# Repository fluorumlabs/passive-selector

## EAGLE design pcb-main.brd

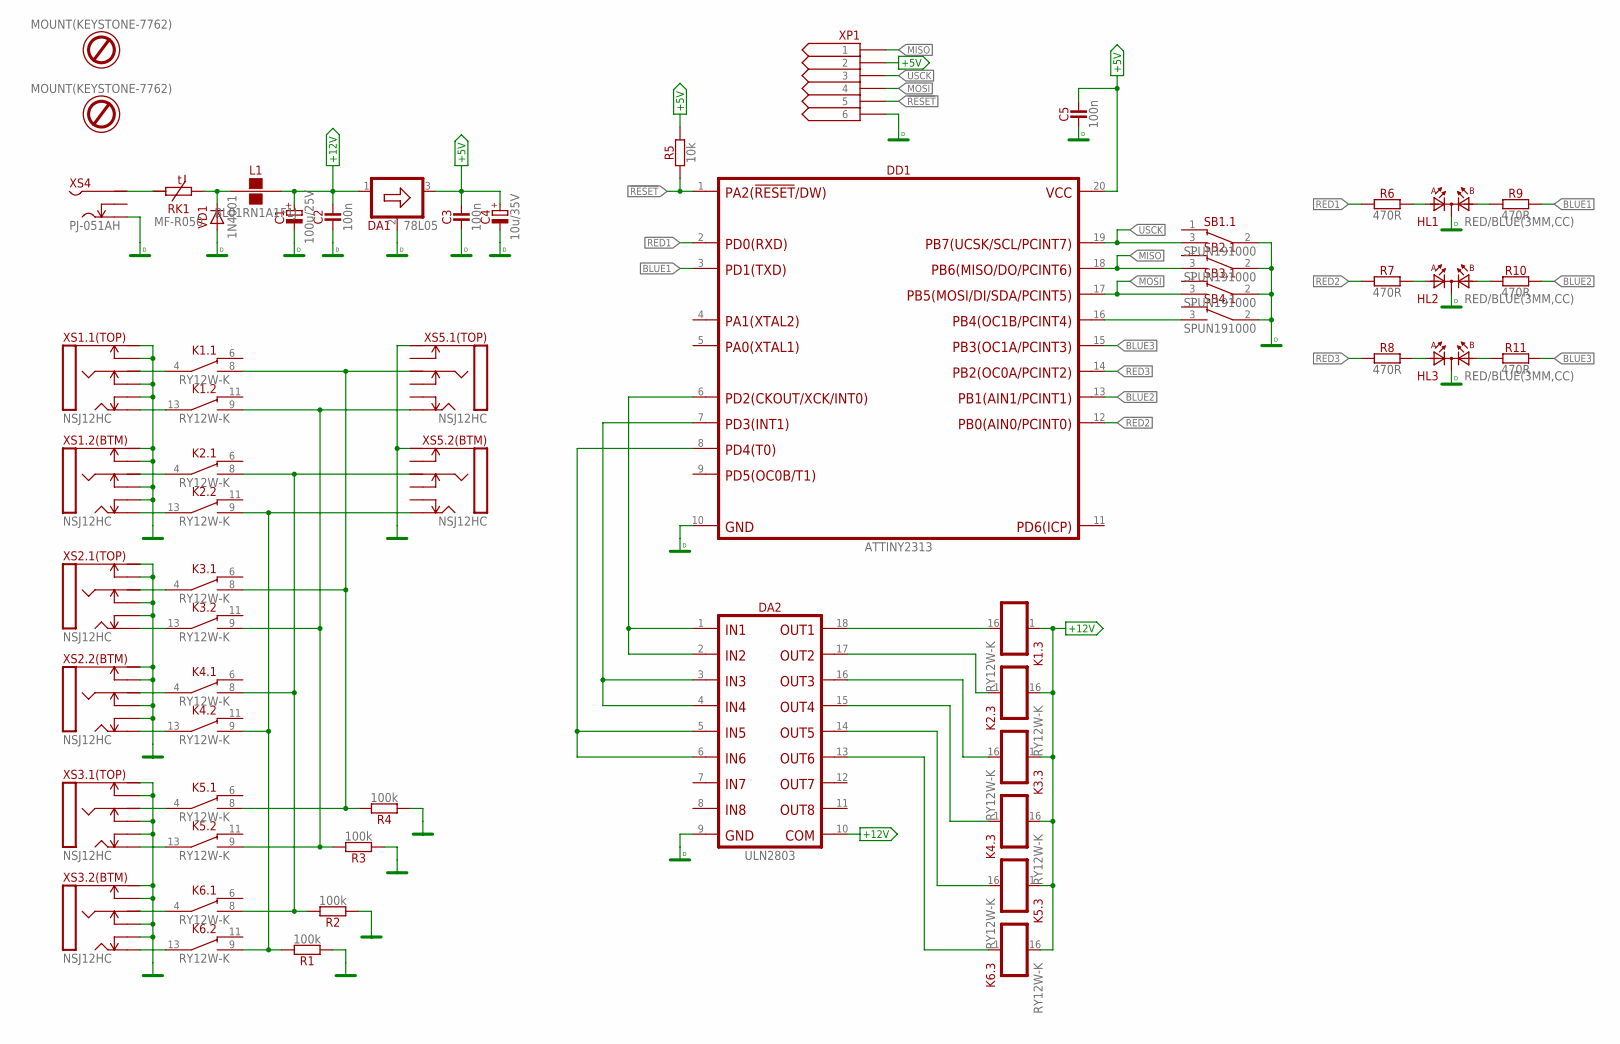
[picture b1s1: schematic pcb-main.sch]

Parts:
C1: 100u/25V; E2,5-7
C2, C3, C5: 100n; C050-024X044
C4: 10u/35V; E2-5
DA1: 78L05; TO92
DA2: ULN2803; DIP-18
DD1: ATTINY2313; DIP-20
HL1, HL2, HL3: RED/BLUE(3MM,CC); DUOLED3MM-H
K1, K2, K3, K4, K5, K6: RY12W-K; RY
L1: BL01RN1A1F1J; BL01RN1A
O1, O2: MOUNT(KEYSTONE-7762); KEYSTONE-7762
R1, R2, R3, R4: 100k; R-0207/10
R5: 10k; R-0207/10
R6, R7, R8, R9, R10, R11: 470R; R-0207/10
RK1: MF-R050; S05K40
SB1, SB2, SB3, SB4: SPUN191000; SPUN-DPDT
VD1: 1N4001; DO41-10
XP1: CONN-6-IDC-LITE; ML6-NO-SHROWD
XS1, XS2, XS3, XS5: NSJ12HC
XS4: PJ-051AH

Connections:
!RESET: DD1.1 (PA2(!RESET/DW)), R5.1, XP1.5
+5V: C3.2, C4.+, C5.2, DA1.3 (OUT), DD1.20 (VCC), R5.2, XP1.2
+12V: C1.+, C2.2, DA1.1 (IN), DA2.10, K1.1 (+), K2.16 (-), K3.1 (+), K4.16 (-), K5.1 (+), K6.16 (-), L1.2
BLUE1: DD1.3 (PD1(TXD)), R9.2
BLUE2: DD1.13 (PB1(AIN1/PCINT1)), R10.2
BLUE3: DD1.15 (PB3(OC1A/PCINT3)), R11.2
DGND: C1.-, C2.1, C3.1, C4.-, C5.1, DA1.2 (GND), DA2.9, DD1.10 (GND), HL1.K, HL2.K, HL3.K, SB1.2 (CM), SB2.2 (CM), SB3.2 (CM), SB4.2 (CM), VD1.A, XP1.6, XS4.3 (S)
GND: R1.1, R2.1, R3.1, R4.1, XS1.RNB (RN), XS1.RNT (RN), XS1.SB (S), XS1.SNB (SN), XS1.SNT (SN), XS1.ST (S), XS1.TNB (TN), XS1.TNT (TN), XS2.RNB (RN), XS2.RNT (RN), XS2.SB (S), XS2.SNB (SN), XS2.SNT (SN), XS2.ST (S), XS2.TNB (TN), XS2.TNT (TN), XS3.RNB (RN), XS3.RNT (RN), XS3.SB (S), XS3.SNB (SN), XS3.SNT (SN), XS3.ST (S), XS3.TNB (TN), XS3.TNT (TN), XS5.SB (S), XS5.ST (S)
MISO: DD1.18 (PB6(MISO/DO/PCINT6)), SB2.3 (NO), XP1.1
MOSI: DD1.17 (PB5(MOSI/DI/SDA/PCINT5)), SB3.3 (NO), XP1.4
unnamed: K1.13 (CM), XS1.TT (T)
unnamed: RK1.1 (A), XS4.1
unnamed: L1.1, RK1.2 (E), VD1.C
unnamed: K1.4 (CM), XS1.RT (R)
unnamed: K2.4 (CM), XS1.RB (R)
unnamed: K2.13 (CM), XS1.TB (T)
unnamed: K3.4 (CM), XS2.RT (R)
unnamed: K3.13 (CM), XS2.TT (T)
unnamed: K4.13 (CM), XS2.TB (T)
unnamed: K4.4 (CM), XS2.RB (R)
unnamed: K6.13 (CM), XS3.TB (T)
unnamed: K6.4 (CM), XS3.RB (R)
unnamed: K5.13 (CM), XS3.TT (T)
unnamed: K5.4 (CM), XS3.RT (R)
unnamed: K1.8 (NO), K3.8 (NO), K5.8 (NO), R4.2, XS5.RT (R)
unnamed: K2.9 (NO), K4.9 (NO), K6.9 (NO), R1.2, XS5.TB (T)
unnamed: K2.8 (NO), K4.8 (NO), K6.8 (NO), R2.2, XS5.RB (R)
unnamed: K1.9 (NO), K3.9 (NO), K5.9 (NO), R3.2, XS5.TT (T)
unnamed: DD1.16 (PB4(OC1B/PCINT4)), SB4.3 (NO)
unnamed: HL1.A1, R6.2
unnamed: HL2.A1, R7.2
unnamed: HL1.A2, R9.1
unnamed: HL2.A2, R10.1
unnamed: HL3.A1, R8.2
unnamed: HL3.A2, R11.1
unnamed: DA2.1, DA2.2, DD1.6 (PD2(CKOUT/XCK/INT0))
unnamed: DA2.3, DA2.4, DD1.7 (PD3(INT1))
unnamed: DA2.5, DA2.6, DD1.8 (PD4(T0))
unnamed: DA2.18, K1.16 (-)
unnamed: DA2.17, K2.1 (+)
unnamed: DA2.16, K3.16 (-)
unnamed: DA2.15, K4.1 (+)
unnamed: DA2.14, K5.16 (-)
unnamed: DA2.13, K6.1 (+)
RED1: DD1.2 (PD0(RXD)), R6.1
RED2: DD1.12 (PB0(AIN0/PCINT0)), R7.1
RED3: DD1.14 (PB2(OC0A/PCINT2)), R8.1
USCK: DD1.19 (PB7(UCSK/SCL/PCINT7)), SB1.3 (NO), XP1.3

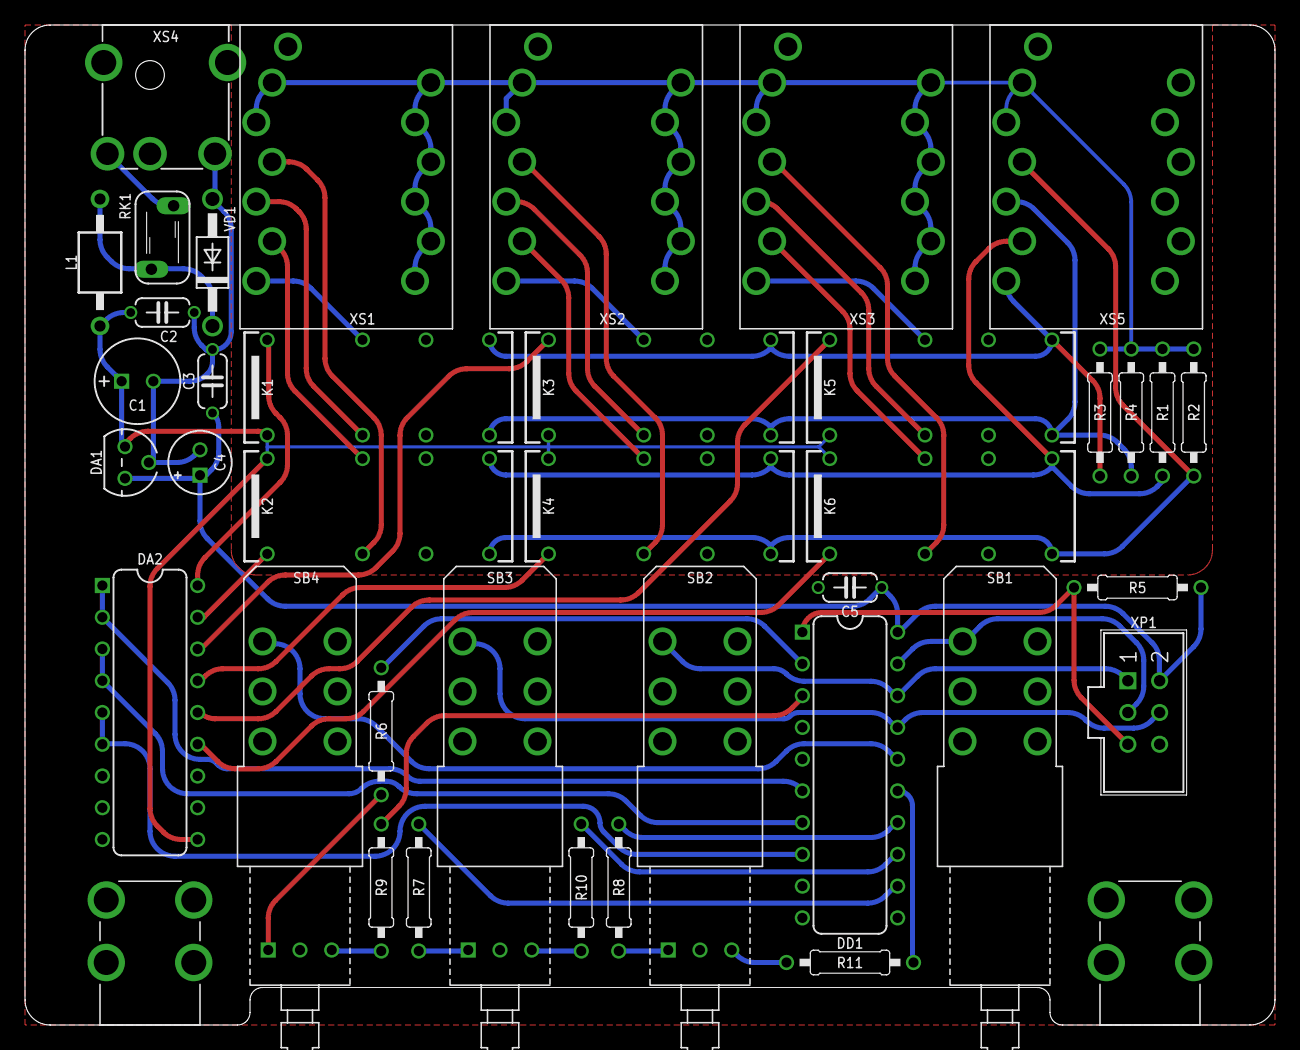
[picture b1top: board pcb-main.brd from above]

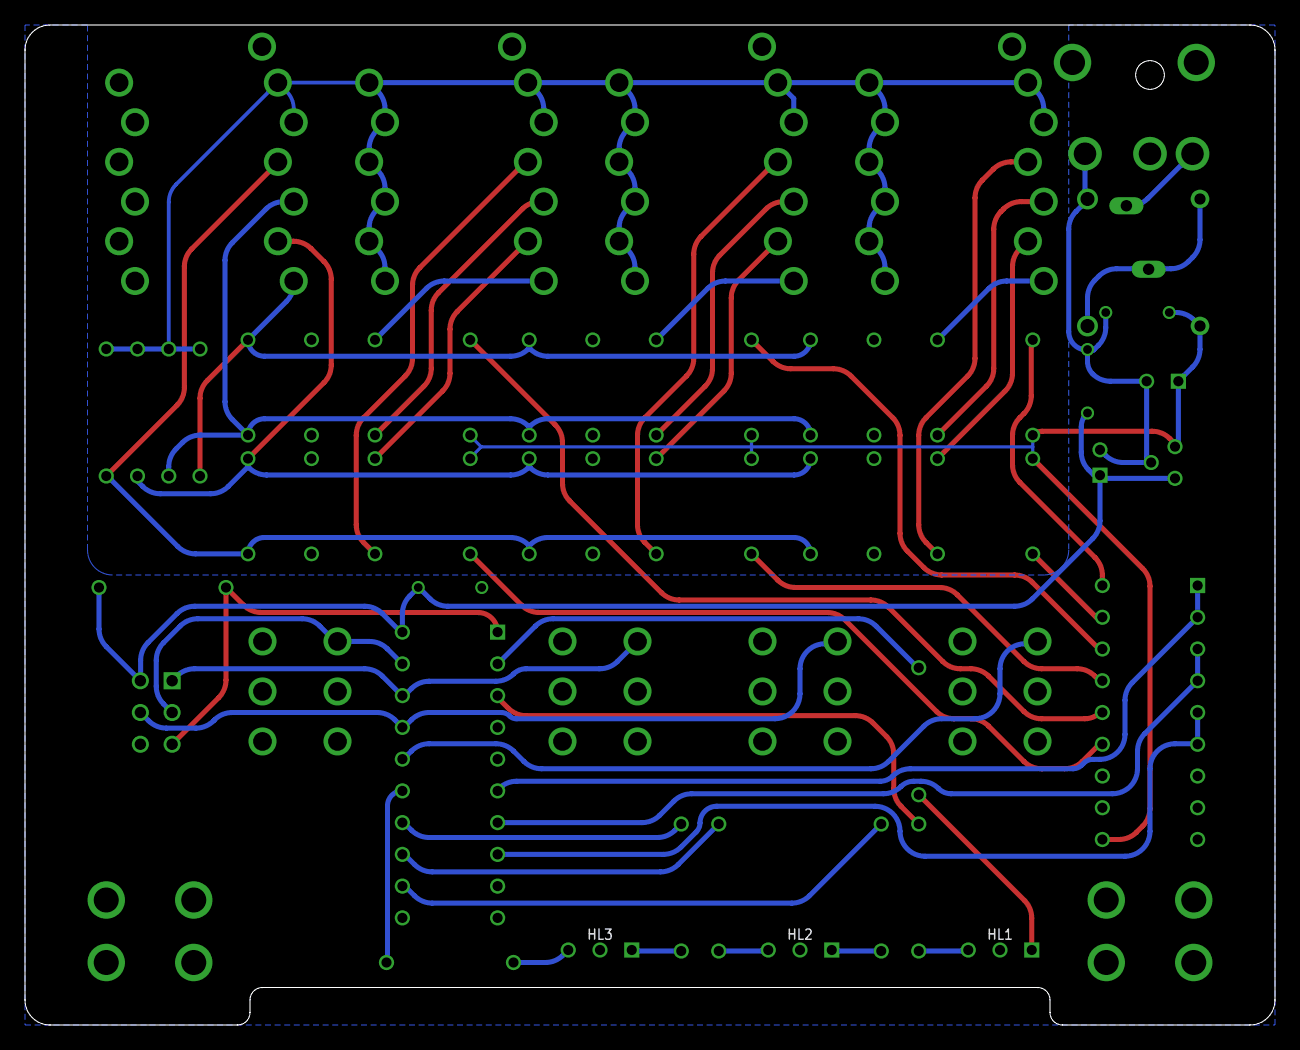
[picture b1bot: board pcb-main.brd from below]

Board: 2 copper layers, 100.0 x 80.0 mm, 44 parts (3 on the bottom side), 48 nets.

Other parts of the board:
E$1: B*-080

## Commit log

2020-12-02 Add .whitesource configuration file
